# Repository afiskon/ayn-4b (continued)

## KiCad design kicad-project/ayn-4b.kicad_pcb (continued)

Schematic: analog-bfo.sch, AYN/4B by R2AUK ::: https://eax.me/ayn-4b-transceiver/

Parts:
C99, C102: 0.1u; C_0805_2012Metric_Pad1.15x1.40mm_HandSolder
C100, C101: 150p; C_0805_2012Metric_Pad1.15x1.40mm_HandSolder
C103: 1-30p; C_Trim_THD_L7.0mm_W6.5mm_P5.00mm
L12: 18u; D_DO-41_SOD81_P2.54mm_Vertical_AnodeUp
Q17, Q18: MMBT3904; SOT-23
R46: 22; R_0805_2012Metric_Pad1.15x1.40mm_HandSolder
R47, R55: 10K; R_0805_2012Metric_Pad1.15x1.40mm_HandSolder
R48, R56, R57: 1K; R_0805_2012Metric_Pad1.15x1.40mm_HandSolder
Y6: 9.000; Crystal_HC49-U_Vertical

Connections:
+12V: R46.1; also elsewhere on the board
ANALOG_BFO: C102.1; also elsewhere on the board
GND: C99.2, C101.2, C103.2, R55.2, R56.2, R57.2; also elsewhere on the board
unnamed: C99.1, Q17.3 (C), Q18.3 (C), R46.2, R47.1
unnamed: C100.1, Q17.1 (B), R47.2, R55.1, Y6.2
unnamed: C100.2, C101.1, Q17.2 (E), R48.2, R56.1
unnamed: C102.2, Q18.2 (E), R57.1
unnamed: C103.1, L12.1
unnamed: L12.2, Y6.1
unnamed: Q18.1 (B), R48.1

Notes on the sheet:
The oscillator should be tuned to: (crystal filter center frequency) - 700 Hz Example: Filter CF = 8.998.280 Hz Osc. Freq = 8.997.580 Hz The expected output power to 50 Ohms is about 4 dBm on the main frequency (probably, mismatched). This is not exactly 7 dBm typically required for a double balanc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
The secret of a superheterodyne receiver free of spurious signals is a clean BFO. The signal of Si5351 is way too dirty and can’t be used as a BFO. Trust me, I’ve tried many times.

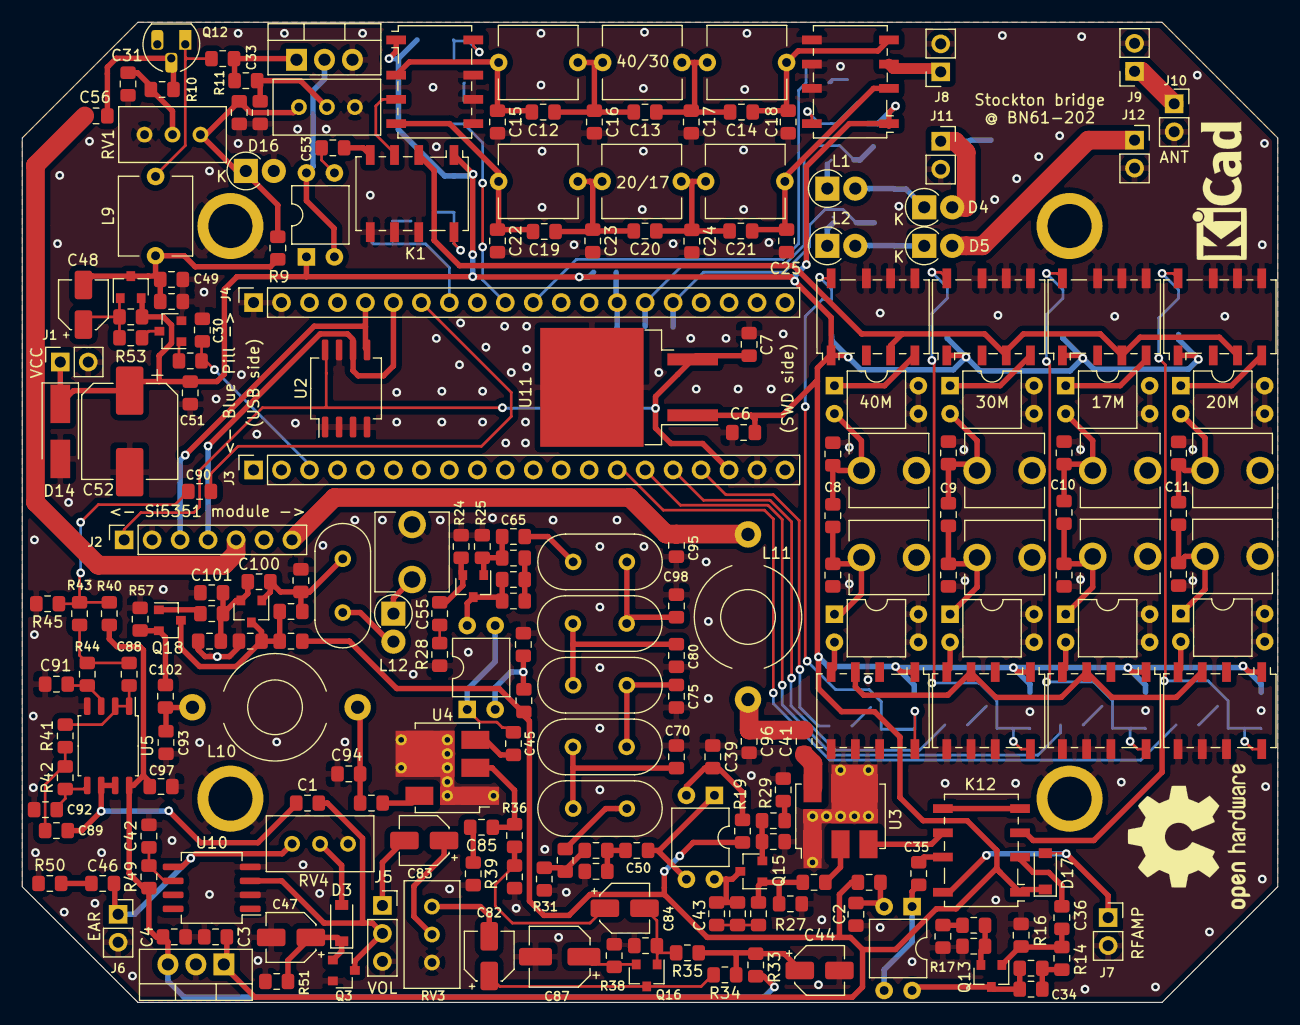
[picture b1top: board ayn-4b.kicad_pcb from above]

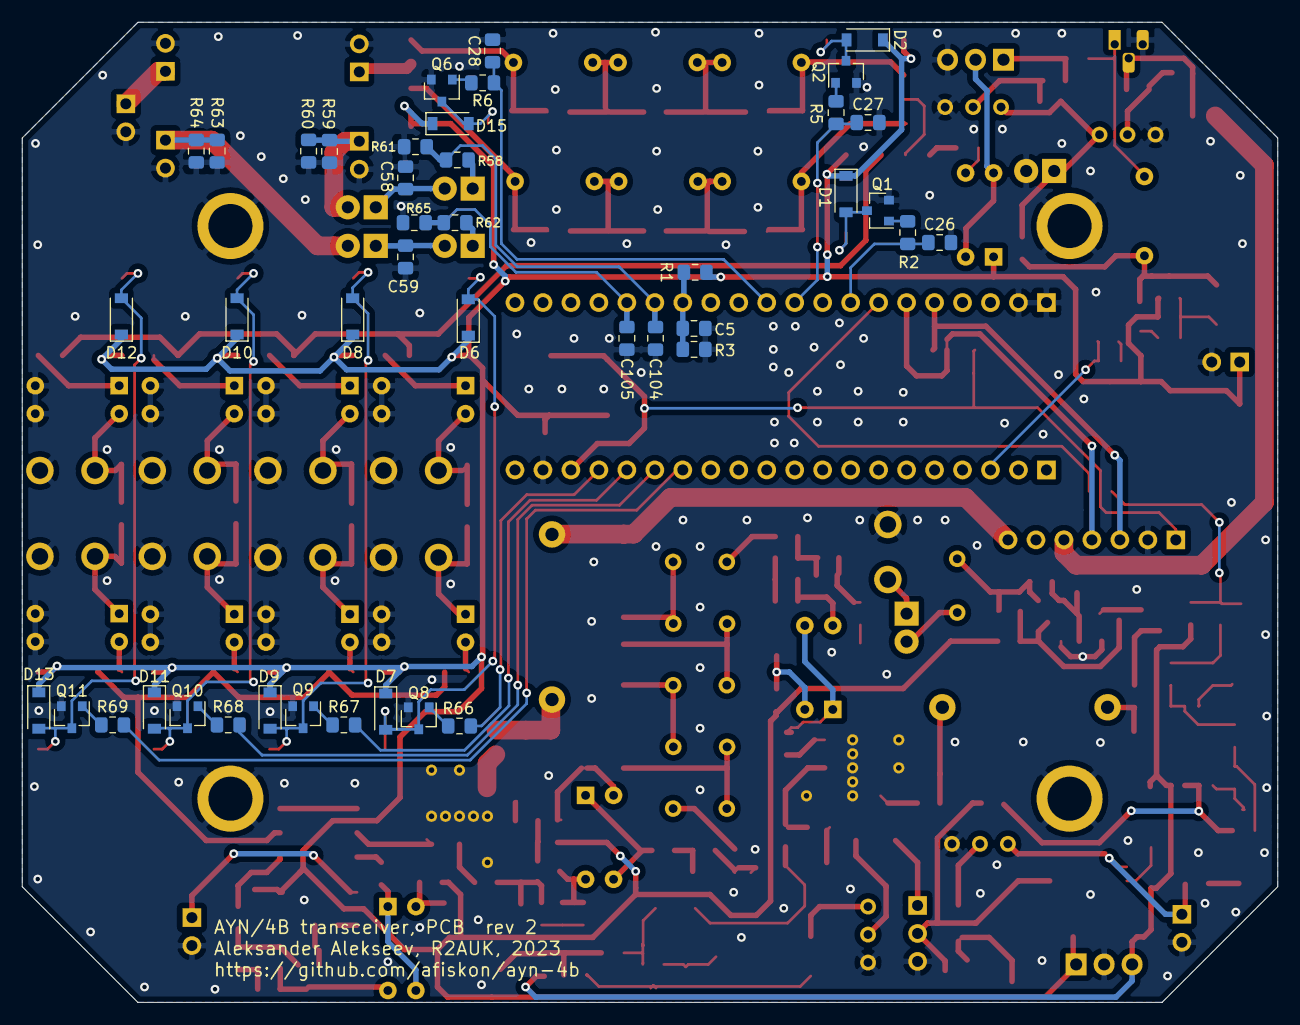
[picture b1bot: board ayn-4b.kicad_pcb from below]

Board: 2 copper layers, 114.0 x 89.0 mm, 278 parts (43 on the bottom side), 153 nets.

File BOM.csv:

Reference, Quantity, Value, Footprint
C1 C93 C94 ,3,470p,Capacitor_SMD:C_0805_2012Metric_Pad1.15x1.40mm_HandSolder
C10 ,1,3.9p,Capacitor_SMD:C_0805_2012Metric_Pad1.15x1.40mm_HandSolder
C11 ,1,5.6p,Capacitor_SMD:C_0805_2012Metric_Pad1.15x1.40mm_HandSolder
C14 C95 C96 ,3,220p,Capacitor_SMD:C_0805_2012Metric_Pad1.15x1.40mm_HandSolder
C13 C15 C16 C17 ,4,330p,Capacitor_SMD:C_0805_2012Metric_Pad1.15x1.40mm_HandSolder
C19 ,1,33p,Capacitor_SMD:C_0805_2012Metric_Pad1.15x1.40mm_HandSolder
C3 C6 ,2,0.47u,Capacitor_SMD:C_0805_2012Metric_Pad1.15x1.40mm_HandSolder
C2 C4 C5 C7 C26 C27 C28 C29 C30 C31 C32 C34 C35 C36 C37 C38 C39 C40 C41 C42 C43 C45 C49 C50 C51 C53 C54 C55 C57 C81 C88 C89 C90 C91 C92 C97 C99 C102 C104 C105 ,40,0.1u,Capacitor_SMD:C_0805_2012Metric_Pad1.15x1.40mm_HandSolder
C46 C86 ,2,0.047u,Capacitor_SMD:C_0805_2012Metric_Pad1.15x1.40mm_HandSolder
C44 C47 C82 C83 C84 ,5,10u,Capacitor_SMD:CP_Elec_4x5.4
C48 ,1,2.2u,Capacitor_SMD:CP_Elec_4x5.4
C52 ,1,220u,Capacitor_SMD:CP_Elec_8x10.5
C60 C65 C70 C75 C80 C98 ,6,270p,Capacitor_SMD:C_0805_2012Metric_Pad1.15x1.40mm_HandSolder
C18 C20 C21 C22 C23 C24 C61 C64 C100 C101 ,10,150p,Capacitor_SMD:C_0805_2012Metric_Pad1.15x1.40mm_HandSolder
C62 C63 C67 C68 C72 C73 C77 C78 C103 ,9,1-30p,My_Library:C_Trim_THD_L7.0mm_W6.5mm_P5.00mm
C66 C69 ,2,100p,Capacitor_SMD:C_0805_2012Metric_Pad1.15x1.40mm_HandSolder
C71 C74 ,2,47p,Capacitor_SMD:C_0805_2012Metric_Pad1.15x1.40mm_HandSolder
C12 C25 C76 C79 ,4,68p,Capacitor_SMD:C_0805_2012Metric_Pad1.15x1.40mm_HandSolder
C8 ,1,15p,Capacitor_SMD:C_0805_2012Metric_Pad1.15x1.40mm_HandSolder
C33 C56 C58 C59 C85 ,5,0.01u,Capacitor_SMD:C_0805_2012Metric_Pad1.15x1.40mm_HandSolder
C87 ,1,22u,Capacitor_SMD:CP_Elec_5x5.4
C9 ,1,8p,Capacitor_SMD:C_0805_2012Metric_Pad1.15x1.40mm_HandSolder
D1 D2 D3 D6 D7 D8 D9 D10 D11 D12 D13 D15 D17 ,13,1N4148W,Diode_SMD:D_SOD-123
D14 ,1,SS14,Diode_SMD:D_SMA_Handsoldering
D16 ,1,1N4736A,Diode_THT:D_DO-41_SOD81_P2.54mm_Vertical_AnodeUp
D4 D5 ,2,1N34/D311 matched pair,Diode_THT:D_DO-41_SOD81_P2.54mm_Vertical_AnodeUp
K1 K2 K3 K4 K5 K6 K7 K8 K9 K10 K11 K12 ,12,G6K-2F-Y (or: HFD4/12-S),Relay_SMD:Relay_DPDT_Omron_G6K-2F-Y
Q1 Q2 Q5 Q6 Q8 Q9 Q10 Q11 Q13 Q14 Q15 Q16 Q17 Q18 ,14,MMBT3904,Package_TO_SOT_SMD:SOT-23
Q12 ,1,BS170,Package_TO_SOT_THT:TO-92_Inline
Q3 ,1,MMBF170,Package_TO_SOT_SMD:SOT-23
Q4 ,1,MMBT3906,Package_TO_SOT_SMD:SOT-23
Q7 ,1,IRF510,Package_TO_SOT_THT:TO-220-3_Vertical
R1 ,1,15K,Resistor_SMD:R_0805_2012Metric_Pad1.15x1.40mm_HandSolder
R11 ,1,220,Resistor_SMD:R_0805_2012Metric_Pad1.15x1.40mm_HandSolder
R14 R21 R23 ,3,1.3K,Resistor_SMD:R_0805_2012Metric_Pad1.15x1.40mm_HandSolder
R15 R24 R26 ,3,68,Resistor_SMD:R_0805_2012Metric_Pad1.15x1.40mm_HandSolder
R17 R28 R29 ,3,6.2,Resistor_SMD:R_0805_2012Metric_Pad1.15x1.40mm_HandSolder
R2 R5 R6 R54 R66 R67 R68 R69 ,8,4.7K,Resistor_SMD:R_0805_2012Metric_Pad1.15x1.40mm_HandSolder
R3 ,1,2.7K,Resistor_SMD:R_0805_2012Metric_Pad1.15x1.40mm_HandSolder
R30 R31 ,2,150,Resistor_SMD:R_0805_2012Metric_Pad1.15x1.40mm_HandSolder
R32 ,1,36,Resistor_SMD:R_0805_2012Metric_Pad1.15x1.40mm_HandSolder
R33 R59 R60 R63 R64 ,5,100,Resistor_SMD:R_0805_2012Metric_Pad1.15x1.40mm_HandSolder
R34 R53 ,2,2.2K,Resistor_SMD:R_0805_2012Metric_Pad1.15x1.40mm_HandSolder
R35 R40 R45 ,3,100K,Resistor_SMD:R_0805_2012Metric_Pad1.15x1.40mm_HandSolder
R13 R20 R22 R36 ,4,3.3K,Resistor_SMD:R_0805_2012Metric_Pad1.15x1.40mm_HandSolder
R37 ,1,47K,Resistor_SMD:R_0805_2012Metric_Pad1.15x1.40mm_HandSolder
R10 R16 R25 R27 R38 R48 R56 R57 ,8,1K,Resistor_SMD:R_0805_2012Metric_Pad1.15x1.40mm_HandSolder
R39 ,1,51,Resistor_SMD:R_0805_2012Metric_Pad1.15x1.40mm_HandSolder
R4 R9 R41 R42 R43 R44 ,6,1.8K,Resistor_SMD:R_0805_2012Metric_Pad1.15x1.40mm_HandSolder
R12 R18 R19 R46 R49 ,5,22,Resistor_SMD:R_0805_2012Metric_Pad1.15x1.40mm_HandSolder
R50 ,1,10,Resistor_SMD:R_0805_2012Metric_Pad1.15x1.40mm_HandSolder
R51 ,1,1Meg,Resistor_SMD:R_0805_2012Metric_Pad1.15x1.40mm_HandSolder
R52 R61 R65 ,3,680,Resistor_SMD:R_0805_2012Metric_Pad1.15x1.40mm_HandSolder
R47 R55 ,2,10K,Resistor_SMD:R_0805_2012Metric_Pad1.15x1.40mm_HandSolder
R58 R62 ,2,300,Resistor_SMD:R_0805_2012Metric_Pad1.15x1.40mm_HandSolder
RV1 RV2 RV3 RV4 ,4,10K,Potentiometer_THT:Potentiometer_Bourns_3296W_Vertical
U1 ,1,L7805,Package_TO_SOT_THT:TO-220-3_Vertical
U10 ,1,LM386,Package_SO:SO-8_5.3x6.2mm_P1.27mm
U11 ,1,L7805,Package_TO_SOT_SMD:TO-263-2
U2 ,1,24LC64,Package_SO:SO-8_5.3x6.2mm_P1.27mm
U3 U4 ,2,ADE-6 (or: ADE-1/ADE-1L/ADE-2),RF_Mini-Circuits:Mini-Circuits_CD542_LandPatternPL-052
U5 ,1,NE5532,Package_SO:SOIC-8_5.23x5.23mm_P1.27mm
Y1 Y2 Y3 Y4 Y5 Y6 ,6,"9 Mhz, see notes",
T1 T2 T3 T12 L9,5,FT37-43,
T4 T5 T6 T7 T8 T9 T10 T11 L3 L4 L5 L6 L7 L8 L10 L11 ,16,T37-6,
J8 J9 J11 J12 ,1,BN61-202,
L1 L2 ,2,1000u,
L12 ,1,18u,
J2 ,1,Si5351 Module,
J3 J4 ,1,Blue Pill,

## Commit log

2023-03-12 Move project from a sandbox repository
2023-03-12 Copy stl-files/ from AYN/DC project
2023-03-12 Add images/
2023-03-12 Minor changes
2026-01-26 Add firmware/build/main.{bin,hex}
